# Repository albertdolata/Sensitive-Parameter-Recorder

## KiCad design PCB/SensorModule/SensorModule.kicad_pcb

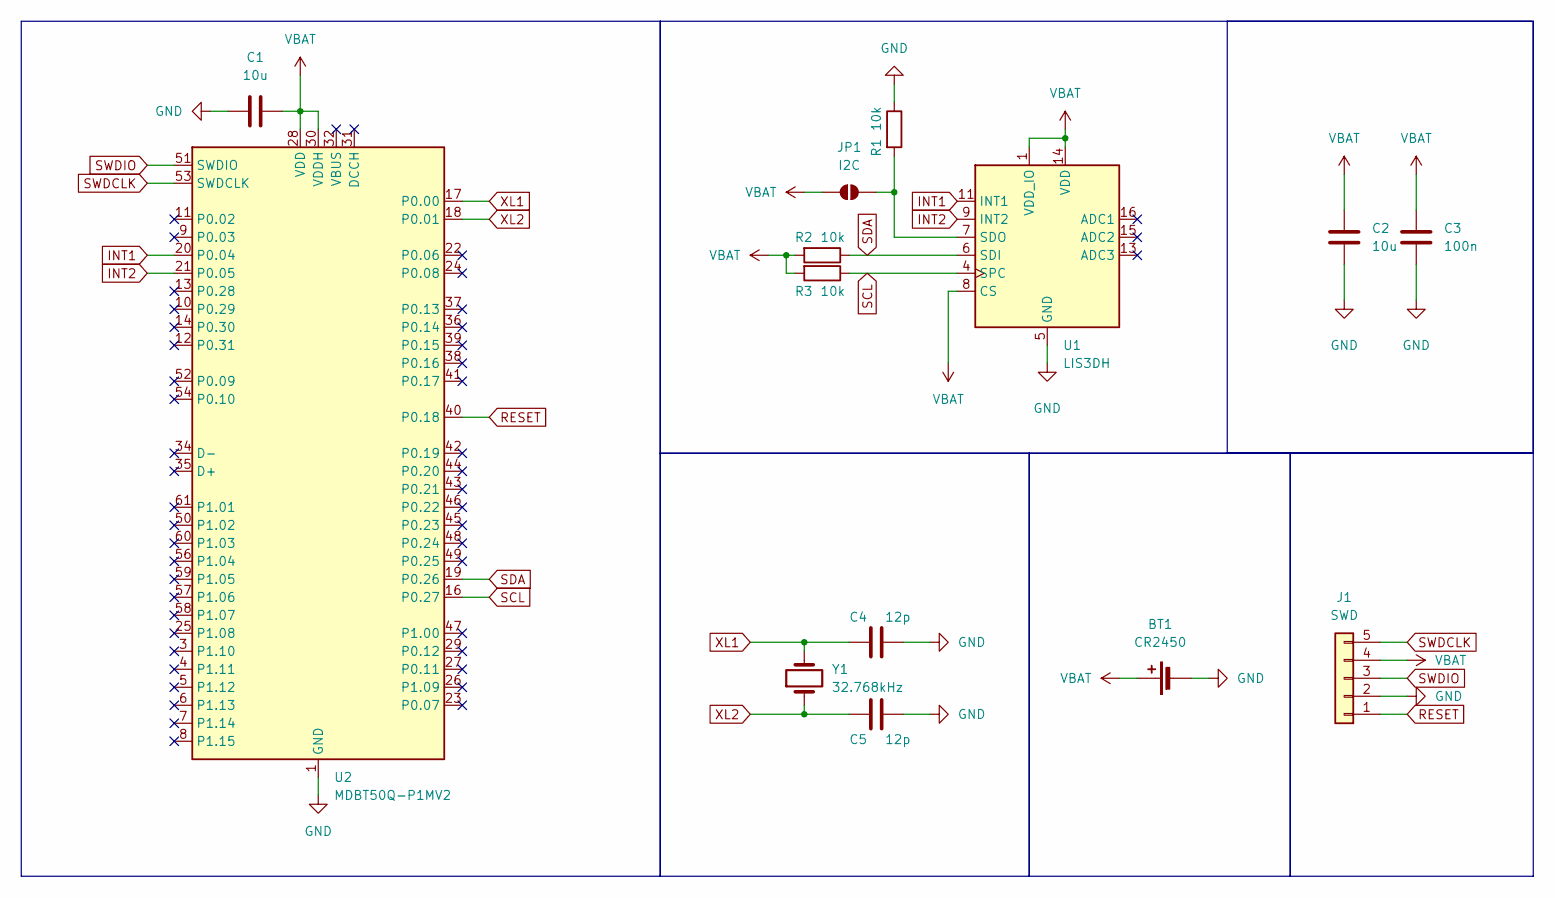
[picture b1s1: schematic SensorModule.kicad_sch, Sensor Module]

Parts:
BT1: CR2450; BatteryHolder_ComfortableElectronic_CH273-2450_1x2450
C1, C2: 10u; C_0402_1005Metric
C3: 100n; C_0402_1005Metric
C4, C5: 12p; C_0402_1005Metric
J1: SWD; PinHeader_1x05_P1.00mm_Vertical_SMD_Pin1Right
JP1: I2C; SolderJumper-2_P1.3mm_Open_TrianglePad1.0x1.5mm
R1, R2, R3: 10k; R_0402_1005Metric
U1: LIS3DH; LGA-16_3x3mm_P0.5mm_LayoutBorder3x5y
U2: MDBT50Q-P1MV2; Raytac_MDBT50Q
Y1: 32.768kHz; Crystal_SMD_3215-2Pin_3.2x1.5mm

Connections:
GND: BT1.2 (-), C1.1, C2.2, C3.2, C4.2, C5.2, J1.2, R1.1, U1.5 (GND), U1.10 (GND), U1.12 (GND), U2.1 (GND), U2.2 (GND), U2.15 (GND), U2.33 (GND), U2.55 (GND)
INT1: U1.11 (INT1), U2.20 (P0.04)
INT2: U1.9 (INT2), U2.21 (P0.05)
unnamed: JP1.1 (A), R1.2, U1.7 (SDO)
RESET: J1.1, U2.40 (P0.18)
SCL: R3.1, U1.4 (SPC), U2.16 (P0.27)
SDA: R2.1, U1.6 (SDI), U2.19 (P0.26)
SWDCLK: J1.5, U2.53 (SWDCLK)
SWDIO: J1.3, U2.51 (SWDIO)
VBAT: BT1.1 (+), C1.2, C2.1, C3.1, J1.4, JP1.2 (B), R2.2, R3.2, U1.1 (VDD_IO), U1.8 (CS), U1.14 (VDD), U2.28 (VDD), U2.30 (VDDH)
XL1: C4.1, U2.17 (P0.00), Y1.2
XL2: C5.1, U2.18 (P0.01), Y1.1

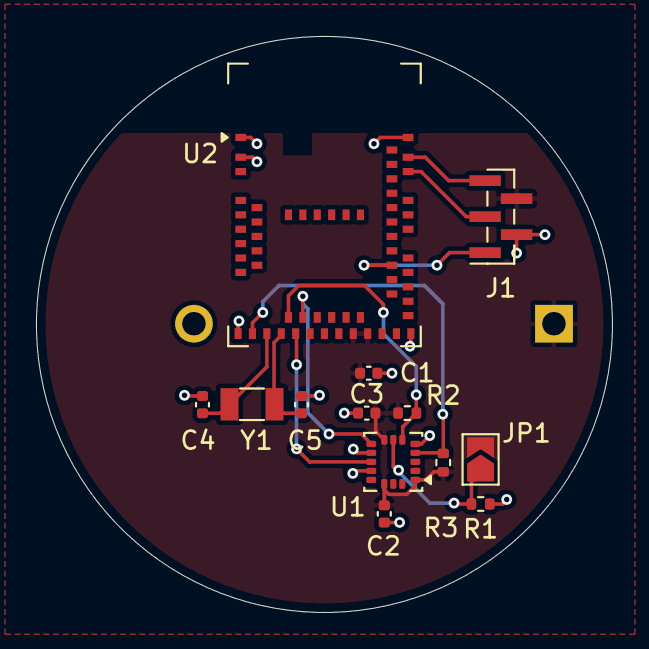
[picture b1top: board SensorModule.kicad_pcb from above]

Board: 2 copper layers, 32.0 x 32.0 mm, 14 parts (1 on the bottom side), 12 nets.

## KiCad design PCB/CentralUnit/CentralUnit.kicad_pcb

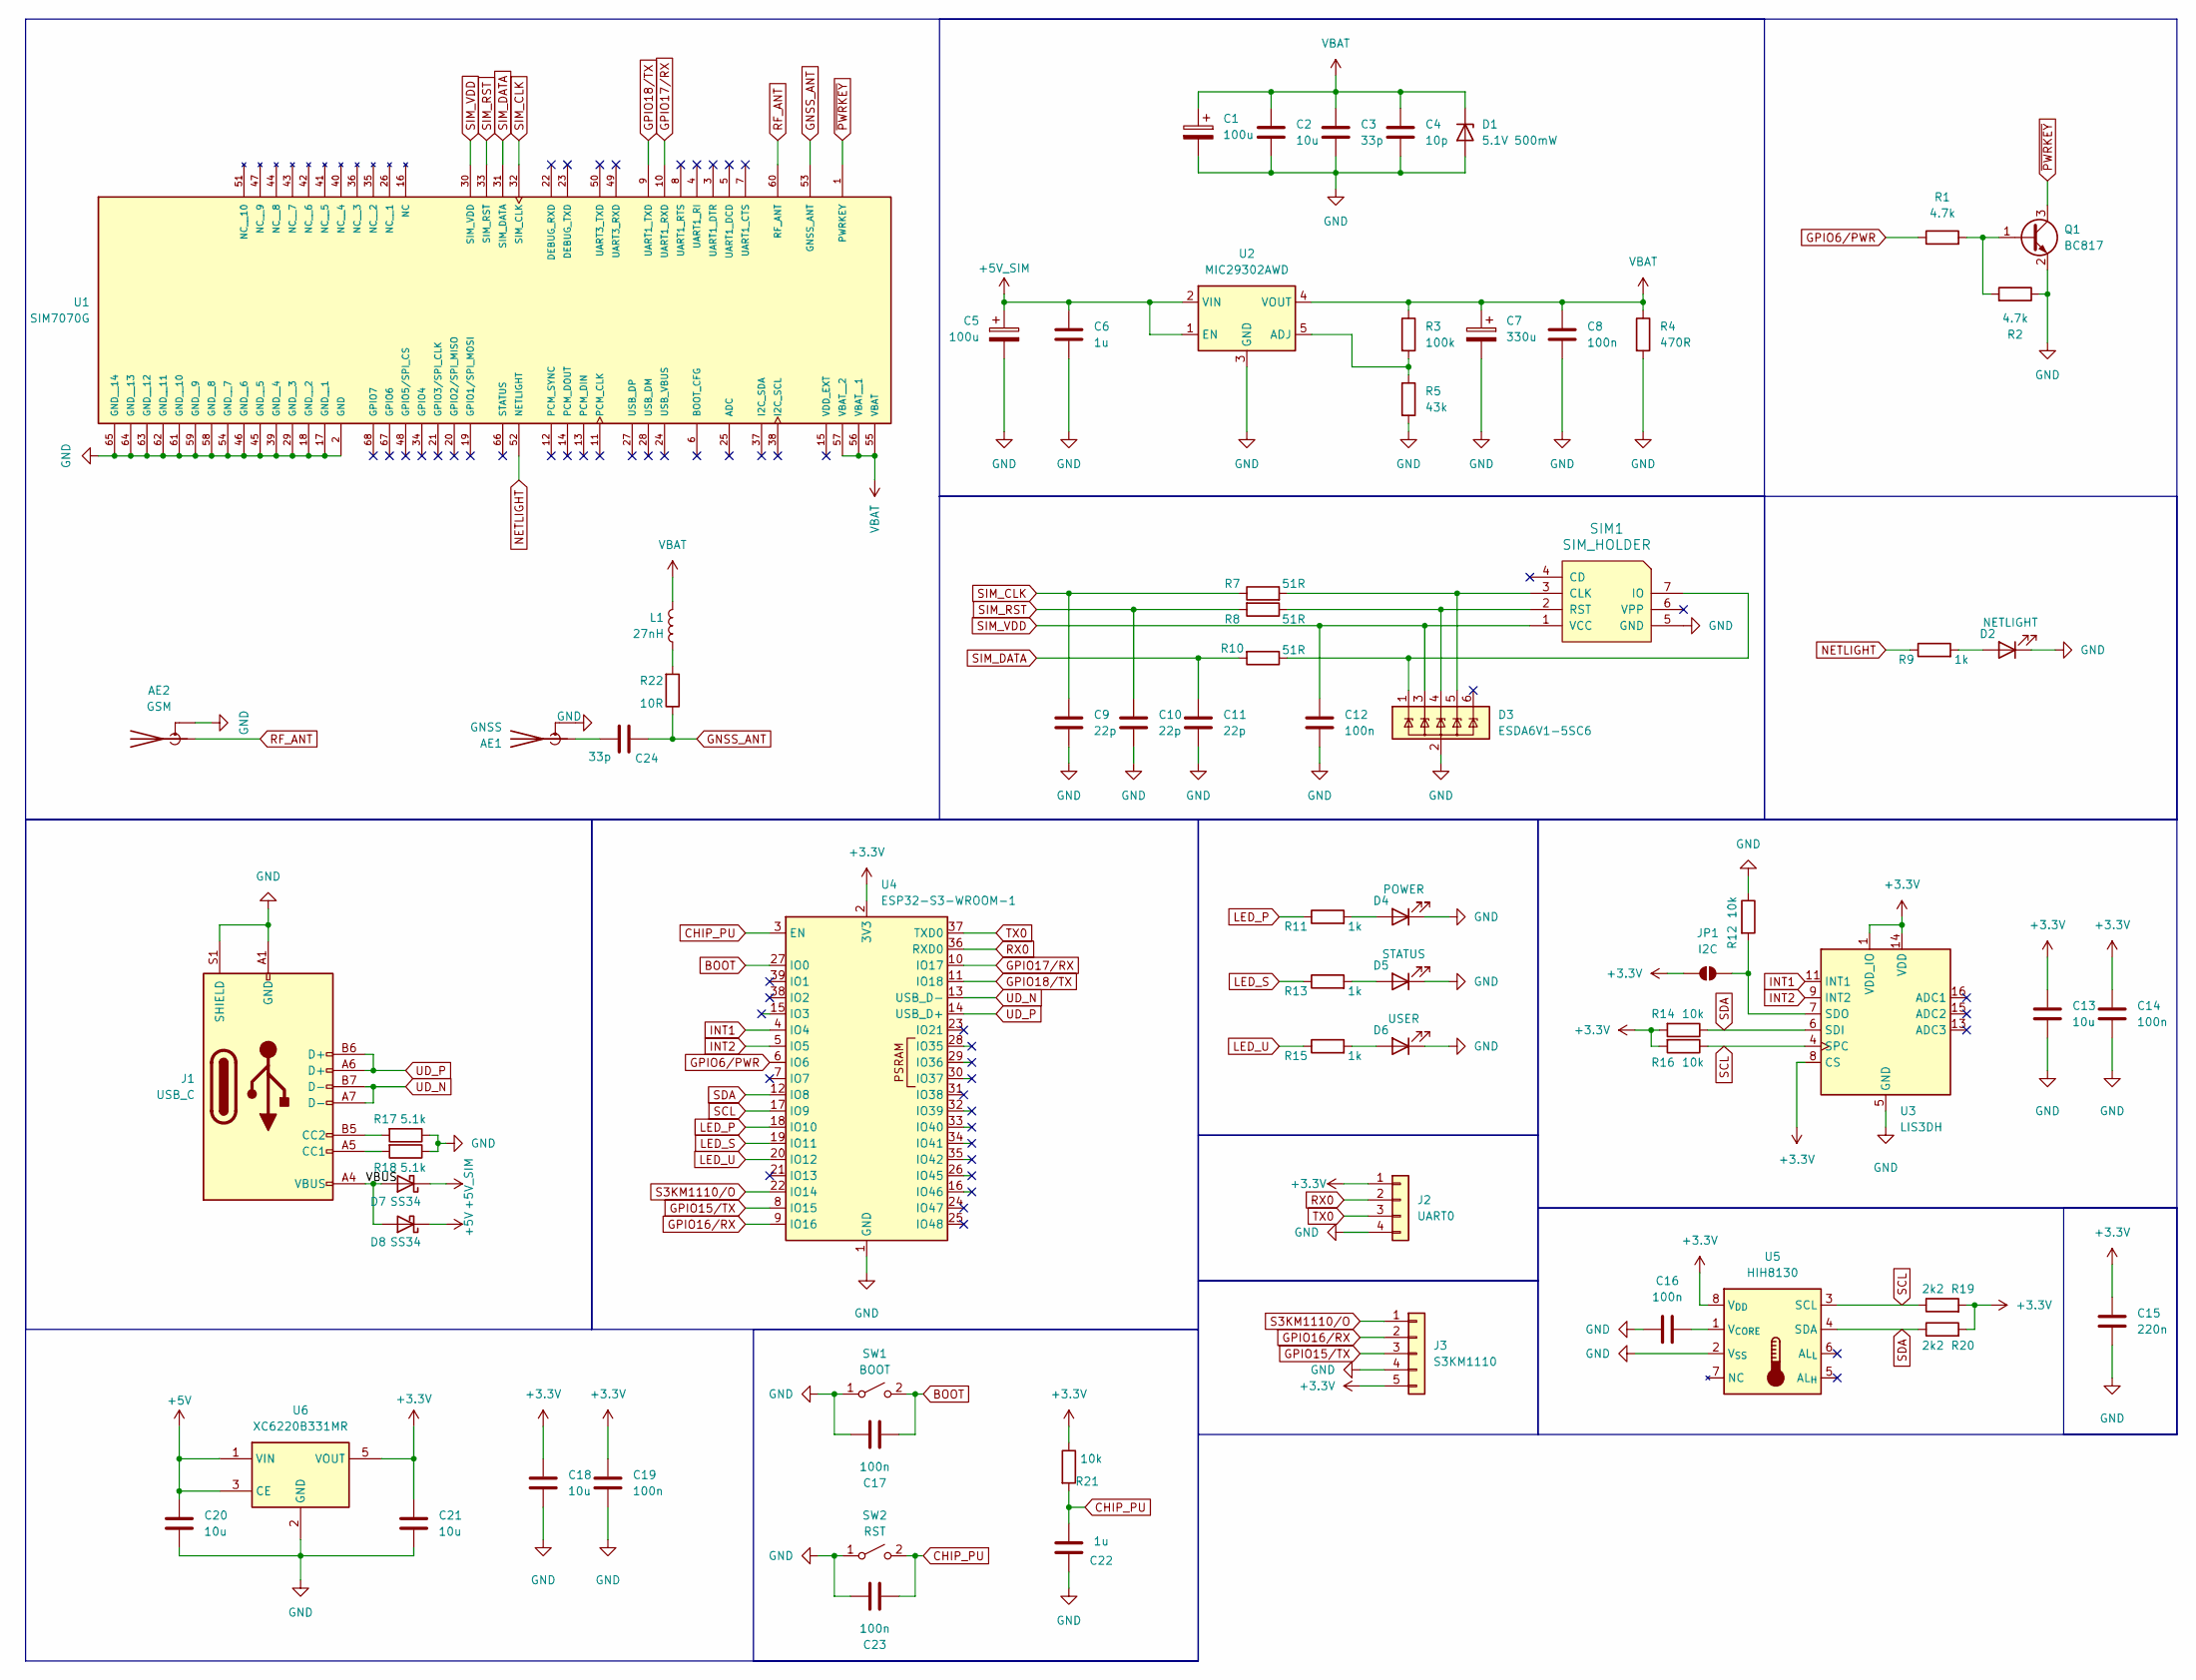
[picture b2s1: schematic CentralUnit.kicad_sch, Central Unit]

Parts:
AE1: GNSS; U.FL_Molex_MCRF_73412-0110_Vertical
AE2: GSM; U.FL_Molex_MCRF_73412-0110_Vertical
C1, C5: 100u; CP_EIA-3216-18_Kemet-A
C2, C13, C18, C20, C21: 10u; C_0402_1005Metric
C3, C24: 33p; C_0402_1005Metric
C4: 10p; C_0402_1005Metric
C6, C22: 1u; C_0402_1005Metric
C7: 330u; CP_EIA-6032-28_Kemet-C
C8, C12, C14, C16, C17, C19, C23: 100n; C_0402_1005Metric
C9, C10, C11: 22p; C_0402_1005Metric
C15: 220n; C_0402_1005Metric
D1: 5.1V 500mW; Nexperia_CFP3_SOD-123W
D2: NETLIGHT; LED_0805_2012Metric
D3: ESDA6V1-5SC6; SOT-23-6
D4: POWER; LED_0805_2012Metric
D5: STATUS; LED_0805_2012Metric
D6: USER; LED_0805_2012Metric
D7, D8: SS34; D_SMA
J1: USB_C; USB_C_Receptacle_HRO_TYPE-C-31-M-12
J2: UART0; PinHeader_1x04_P1.00mm_Vertical_SMD_Pin1Left
J3: S3KM1110; PinHeader_1x05_P2.54mm_Vertical
JP1: I2C; SolderJumper-2_P1.3mm_Open_TrianglePad1.0x1.5mm
L1: 27nH; L_0402_1005Metric
Q1: BC817; SOT-23
R1, R2: 4.7k; R_0402_1005Metric
R3: 100k; R_0402_1005Metric
R4: 470R; R_0402_1005Metric
R5: 43k; R_0402_1005Metric
R7, R8, R10: 51R; R_0402_1005Metric
R9, R11, R13, R15: 1k; R_0402_1005Metric; PART FIELD 1 ÌùÆ¬µç×è
R12, R14, R16, R21: 10k; R_0402_1005Metric
R17, R18: 5.1k; R_0402_1005Metric
R19, R20: 2k2; R_0402_1005Metric
R22: 10R; R_0402_1005Metric
SIM1: SIM_HOLDER; nanoSIM_SMN-303
SW1: BOOT; SW_Tactile_SPST_NO_Straight_CK_PTS636Sx25SMTRLFS
SW2: RST; SW_Tactile_SPST_NO_Straight_CK_PTS636Sx25SMTRLFS
U1: SIM7070G; SIM7070G_MODULE_SIM7070G; PARTREV V1.03
U2: MIC29302AWD; TO-252-5_1.27mm_TabPin3
U3: LIS3DH; LGA-16_3x3mm_P0.5mm_LayoutBorder3x5y
U4: ESP32-S3-WROOM-1
U5: HIH8130; SOIC-8_3.9x4.9mm_P1.27mm
U6: XC6220B331MR; SOT-23-5

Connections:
+3.3V: C13.1, C14.1, C15.1, C18.1, C19.1, C21.1, J2.1, J3.5, JP1.2 (B), R14.2, R16.2, R19.2, R20.2, R21.1, U3.1 (VDD_IO), U3.8 (CS), U3.14 (VDD), U4.2 (3V3), U5.8 (V_{DD}), U6.5 (VOUT)
+5V: C20.1, D8.1 (K), U6.1 (VIN), U6.3 (CE)
+5V_SIM: C5.1, C6.1, D7.1 (K), U2.1 (EN), U2.2 (VIN)
/VBUS: D7.2 (A), D8.2 (A), J1.A4 (VBUS), J1.A9 (VBUS), J1.B4 (VBUS), J1.B9 (VBUS)
BOOT: C17.2, SW1.2 (B), U4.27 (IO0)
CHIP_PU: C22.2, C23.2, R21.2, SW2.2 (B), U4.3 (EN)
GND: AE1.2 (Shield), AE2.2 (Shield), C1.2, C2.2, C3.2, C4.2, C5.2, C6.2, C7.2, C8.2, C9.2, C10.2, C11.2, C12.2, C13.2, C14.2, C15.2, C16.1, C17.1, C18.2, C19.2, C20.2, C21.2, C22.1, C23.1, D1.2 (A), D2.1 (K), D3.2 (GND), D4.1 (K), D5.1 (K), D6.1 (K), J1.A1 (GND), J1.A12 (GND), J1.B1 (GND), J1.B12 (GND), J1.S1 (SHIELD), J2.4, J3.4, Q1.2 (E), R2.1, R4.2, R5.2, R12.1, R17.1, R18.1, SIM1.5 (GND), SIM1.SH, SW1.1 (A), SW2.1 (A), U1.2 (GND), U1.17 (GND__1), U1.18 (GND__2), U1.29 (GND__3), U1.39 (GND__4), U1.45 (GND__5), U1.46 (GND__6), U1.54 (GND__7), U1.58 (GND__8), U1.59 (GND__9), U1.61 (GND__10), U1.62 (GND__11), U1.63 (GND__12), U1.64 (GND__13), U1.65 (GND__14), U2.3 (GND), U3.5 (GND), U3.10 (GND), U3.12 (GND), U4.1 (GND), U4.40 (GND), U4.41 (GND), U5.2 (V_{SS}), U6.2 (GND)
GNSS_ANT: C24.2, R22.1, U1.53 (GNSS_ANT)
GPIO6/PWR: R1.1, U4.6 (IO6)
GPIO15/TX: J3.3, U4.8 (IO15)
GPIO16/RX: J3.2, U4.9 (IO16)
GPIO17/RX: U1.10 (UART1_RXD), U4.10 (IO17)
GPIO18/TX: U1.9 (UART1_TXD), U4.11 (IO18)
INT1: U3.11 (INT1), U4.4 (IO4)
INT2: U3.9 (INT2), U4.5 (IO5)
LED_P: R11.1, U4.18 (IO10)
LED_S: R13.1, U4.19 (IO11)
LED_U: R15.1, U4.20 (IO12)
NETLIGHT: R9.1, U1.52 (NETLIGHT)
unnamed: AE1.1 (A), C24.1
unnamed: D2.2 (A), R9.2
unnamed: D3.1 (IO1), R10.1, SIM1.7 (IO)
unnamed: D3.4 (IO3), R8.1, SIM1.2 (RST)
unnamed: D3.5 (IO4), R7.2, SIM1.3 (CLK)
unnamed: D4.2 (A), R11.2
unnamed: D5.2 (A), R13.2
unnamed: D6.2 (A), R15.2
unnamed: J1.A5 (CC1), R18.2
unnamed: J1.B5 (CC2), R17.2
unnamed: JP1.1 (A), R12.2, U3.7 (SDO)
unnamed: L1.2, R22.2
unnamed: Q1.1 (B), R1.2, R2.2
unnamed: R3.2, R5.1, U2.5 (ADJ)
unnamed: C16.2, U5.1 (V_{CORE})
RF_ANT: AE2.1 (A), U1.60 (RF_ANT)
RX0: J2.2, U4.36 (RXD0)
S3KM1110/O: J3.1, U4.22 (IO14)
SCL: R16.1, R19.1, U3.4 (SPC), U4.17 (IO9), U5.3 (SCL)
SDA: R14.1, R20.1, U3.6 (SDI), U4.12 (IO8), U5.4 (SDA)
SIM_CLK: C9.1, R7.1, U1.32 (SIM_CLK)
SIM_DATA: C11.1, R10.2, U1.31 (SIM_DATA)
SIM_RST: C10.1, R8.2, U1.33 (SIM_RST)
SIM_VDD: C12.1, D3.3 (IO2), SIM1.1 (VCC), U1.30 (SIM_VDD)
TX0: J2.3, U4.37 (TXD0)
UD_N: J1.A7 (D-), J1.B7 (D-), U4.13 (USB_D-)
UD_P: J1.A6 (D+), J1.B6 (D+), U4.14 (USB_D+)
VBAT: C1.1, C2.1, C3.1, C4.1, C7.1, C8.1, D1.1 (K), L1.1, R3.1, R4.1, U1.55 (VBAT), U1.56 (VBAT__1), U1.57 (VBAT__2), U2.4 (VOUT)
~PWRKEY: Q1.3 (C), U1.1 (PWRKEY)

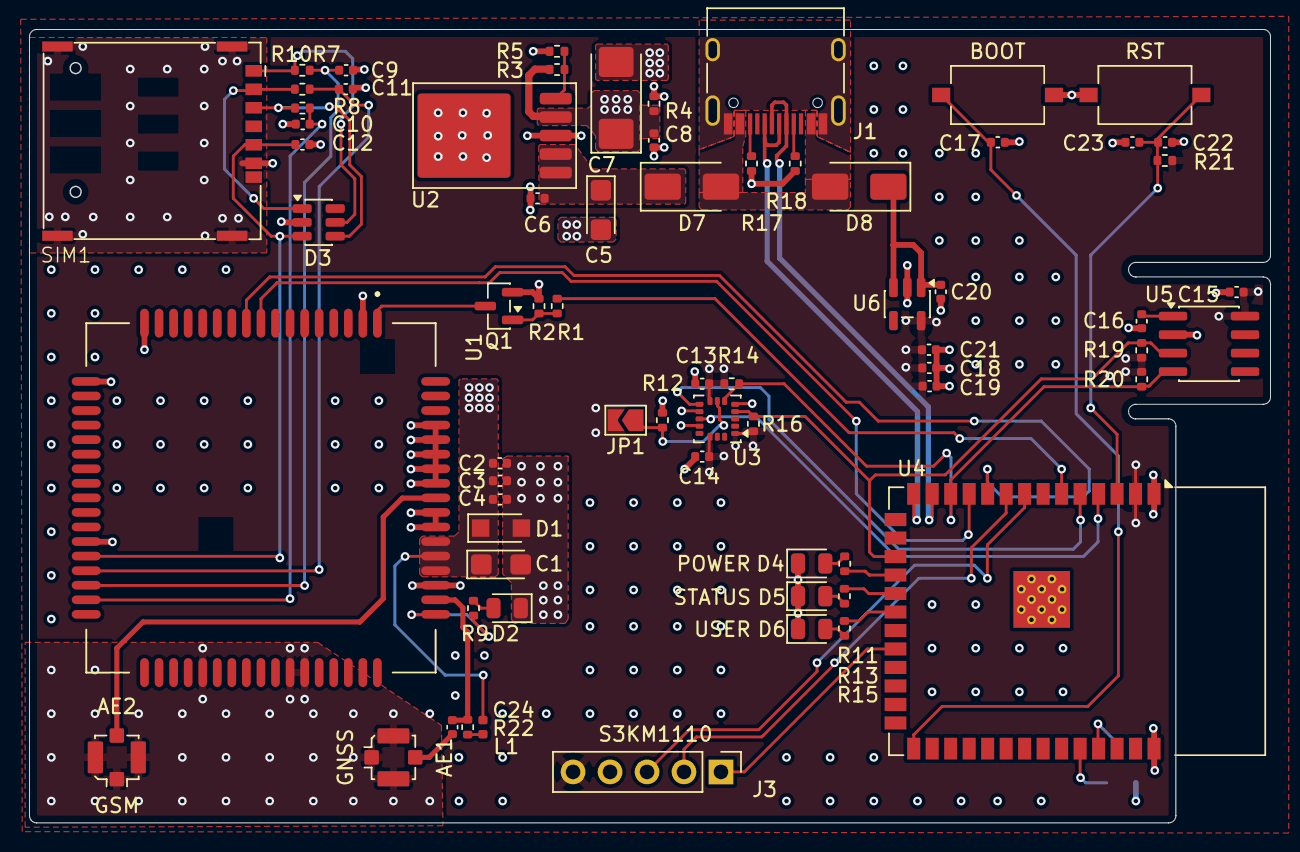
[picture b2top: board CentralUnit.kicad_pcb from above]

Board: 4 copper layers, 85.2 x 54.5 mm, 70 parts (1 on the bottom side), 48 nets.

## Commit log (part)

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2026-04-02 Create project
2026-04-02 Create abstract class Sesnor
2026-04-02 Create class TempHumSenesor
2026-04-02 Create clas AccelSensor
2026-04-02 Create testing programm in main file
2026-04-02 Fix format
2026-04-02 Refactor: add macro for number of sensors, add starting logs, fix delay logic
2026-04-02 Create class ContactSensor
2026-04-02 Create class PresenceSensor
2026-04-02 Change logic of function readData in ContactSensor
2026-04-02 Write code of class PresenceSensor
2026-04-02 Upadte main fucntion, add contact and presence sensor object to the array of sensors
2026-04-02 Create file for CloudManager class
2026-04-02 Add ThingSpeak library to the project
2026-04-02 Write code of class CloudManager
2026-04-02 Refactor class Sensor, add temporery fields for sensor values
2026-04-02 Refactor function readData in class TempHumSensor, store BME230 readings in shared Sensor values1-3
2026-04-02 Refactor classes AccelSensor, ContactSensor, PresennceSensor, now sotres it's reading in shared value Sensor value1
2026-04-02 Fix: moved fields form private to public
2026-04-02 Update main file, add ThingSpeak feature
2026-04-12 Create Bluetooth Sensor Manager file
2026-04-12 Create class BLESensor
2026-04-12 Refactor: Class BLESensorManager now assings recived data to given sensor
2026-04-12 Future: add support of bluetooth
2026-04-12 Future: Add start of BLE radar
2026-04-13 Refactor: Update code to suppport new BLESensors
2026-04-13 Update: class now is supporting 3 sensors
2026-04-13 Refactor: function init constantly return true
2026-04-13 Change in platformio.ini
2026-04-13 Debug: add code for easier debugging while testing with real devices
2026-04-14 Update: extended fields in class Sensor for new data
2026-04-14 Update: changed names of variables for recived data from ble and expected data that should be recived
2026-04-14 Update: deleted field shake - not usuable for prototape, updatethe assigning of values in switch section
2026-04-14 Update: the data that is set in the ThingSpeak fields has been changed
2026-04-26 Create class for GPS service
2026-04-26 Add GPS support to main file
2026-04-26 Variable edit: changed sensor fileds sent to ThingSpeak for debugging
2026-05-04 Add PCB KiCAD 9..0 Files
2026-05-10 pliki z konfiguracją esp32 i simcoma
    Pliki z konfiguracją esp32 i sim7000, funkcję pozwalające uruchomić sim'a, zalogować się do sieci, pobrać parametry stacji bazowej i wysłać przez mqtt. Do dodania, obsługa rzeczywistych sensorów i zb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
2026-05-22 Add new item to ignore
2026-05-22 Moved files to appropriate project code folders
2026-05-22 Add necceseary library to data_send_service.cpp - freertos/queue.h
2026-05-22 expanded the fields of sensor_data_t structure for all sensors
2026-05-22 function send_at_cmd now is global function
2026-05-22 Add declaration of function send_at_cmd in sim7000_core file
2026-05-22 Refactor of class GPSManager - class now is using sent_at_cmd function
2026-05-22 Fix typo
2026-05-22 Integration main code with main code of esp_simcom
2026-05-22 Expand json format in data_send_service
2026-05-22 Commented flags out because by default without specifying bed parameters with zeros - an error
2026-05-29 Change Uart baud rate to fit my simcom in sim7000_core.cpp | fix assignment of current_data schock variable
2026-05-29 Add new field for time stamps of data in sensor_data_t
2026-05-29 Add function to parse time form gps data whichc is called in parseResponse function | Add getter for timestamps parsed by new function
2026-05-29 Add ESP32 internal RTC synchronization with GPS
    - Add setESP32Time() to update internal timer when GPS has fix
    - Update current_data.timestamp to source time from ESP32 RTC
2026-05-29 Create test function for creating file in flash memory, write text into the file and then read text from it
2026-05-29 Create function to save data in flash memory
2026-05-29 Create function to sent backup data by data_service_push()
2026-05-29 Refactor: extract data assignment of sensor_data_t to assignDataToStruct function
2026-05-29 Add data backup logic in main
2026-05-29 Create init function for SPIFFS and add call of it in setup()
2026-05-29 Refactor: extract sim7000 if statements to SIMComInit function
2026-05-29 Refactor: extract sensor table initialization logic to SensorTableInit function
2026-05-29 Refactor: extract BLE logic to BLEInit function
2026-05-29 Refactor: extract readData from sensor logic to readDataFromSensor function
2026-05-29 Refactor: extract data logic to sendDataToServer function
2026-05-29 Fix bugs after testing offline data storing
    - Timestamp is now correctly saved in offline data
    - Fixed looping problem with data recovery from internal flash memory
2026-06-03 Temp-hum sensor driver implementation
2026-06-08 Obsługa sensora mmw
2026-06-12 New JSON data format
2026-06-12 Refactor: changed values for secondary central data
2026-06-12 Refacotr: update class for TH06 sensor
2026-06-12 Refacotr: update class for LIS3DH accelerometer
2026-06-12 Refacotr: update class for S3KM1110 mmWave Radar - easire approach
2026-06-12 Add libraries to the project
2026-06-13 Create new class for BLE pallet sensor
2026-06-13 Create new class for BLE secondary central
2026-06-13 Refactor: BLEPalletSensor now is compatible with nrf sent data
2026-06-13 Refactor: BLESensorManager now is compatible with data sent by nrf
2026-06-15 Fix name of the class
2026-06-15 Create MainCentralSensorManager class
2026-06-15 Refactor: rename struct to fix name collision
2026-06-15 Upadte: add proper fields in struct for sensor data
2026-06-15 Fix comment
2026-06-16 Fix format of file with class MainCentralSensorManager
2026-06-16 Refactor: Integrate MainCentralSensorManager and clean up main.cpp
2026-06-16 Fix: resolve switch case compile error in BLESensorManager
2026-06-16 Fix: update JSON generator with correct fields and data types
2026-06-16 Update: add proper fields to struct for accelerometer data
2026-06-16 Update add accel data in JSON generator
2026-06-16 Update: function fillSensorData now assigns proper data in data struct
2026-06-16 Update project dependencies
2026-06-16 Add usage of LEDs on board
2026-06-16 Update rx/tx pin for hardware
2026-06-16 Update sim init function for testing hardware
2026-06-18 Update: replace the code file for sim7070 configuration
2026-06-18 Rename header file for simcom7070
2026-06-18 Update: Integrate GPSManager with SIM7070E
    - Add pause/resume functions to control GPS power
    - Fix include path
2026-06-18 Fix typos to match proper sim7070 functions
2026-06-18 Fix: Increase stack size for data_sender_task to 8KB
    - Resolves Guru Meditation Error (Stack Overflow) when processing massive offline data backlog from SPIFFS
2026-06-18 Refactor: Update main.cpp for SIM7070E and prepare for hardware tests
    - Rename all sim7000_* function calls to sim7070_* to match the new core
    - Enable global INFO logs and set SIM7070_GPRS to DEBUG level
    - Temporarily comment out GPS routines pending hardware rework
2026-06-23 Refactor: switch to MAC address filtering and remoce second pallet sensor
2026-06-23 Fix: implement MQTT disconnect to prevent RF transceiver crash Resolved hardware-level conflicts in the SIM7070E modem caused by simultaneous RF demands from active PDP/MQTT contexts and GNSS wake-up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
    sim7070_core.h & sim_mod.c:
    - Added sim7070_mqtt_disconnect() to safely terminate MQTT sessions (AT+SMDISC) and deactivate the PDP context (AT+CNACT=0,0).
    - Refactored the IP allocation active polling loop (Active Polling) to improve connection stability and prevent T-Mobile network rejections.
    data_send_service.h & data_send_service.cpp:
    - Updated the data_sender_task to monitor queue size via uxQueueMessagesWaiting().
    - The background task now explicitly closes all network connections when
2026-06-23 Refactor: add MAC addresses and implement initial GPS fix waiting
2026-06-25 Fix: cell data is now correctly recived from simcom
2026-06-25 refactor: restructure offline storage and prevent FSM deadlocks
    - Relocate SPIFFS backup logic to data_send_service to decouple it from main state machine.
    - Reduce data_queue size to 1 and trigger automatic SPIFFS save on RAM full.
    - Remove blocking vTaskDelay in data_sender_task to prevent GSM/GNSS RF collisions.
    - Increase JSON buffer to 768 bytes and add motion_detected_p1 (p1mot) to payload.
    - Optimize sendBackupData to bypass RAM queue, reducing Flash memory wear.
2026-06-25 Fix: decouple power state from fix status and resolve state machine bugs
    - Introduce 'fixStatus' to track satellite fix independently from module power state ('isON').
    - Add 'isPowered()' getter to safely expose hardware state to the main state machine.
    - Fix inverted guard clause in 'resume()' and ensure 'fixStatus' and timestamps are cleared on wake.
    - Add guard clause in 'update()' to prevent polling the GNSS baseband when powered off.
    - Remove raw NMEA serial debug prints to reduce log clutter.
2026-06-25 Update: add assignment of 'motion_detected_p1' from palletSensor1 in MainCentralSensorManager
2026-06-26 Refactor: implement non-blocking FSM and decouple core services
    - Replace linear, delay-based main loop with a non-blocking Finite State Machine (FSM).
    - Delegate all SPIFFS offline backup logic entirely to 'data_send_service'.
    - Offload BLE scanning to a dedicated FreeRTOS background task ('bleScanTask') pinned to Core 0.
    - Add 120-second timeout for GNSS fix acquisition in State 0 to prevent FSM stalling.
    - Implement Anti-Spoofing logic (FSM State 1) to fetch BTS cell info with a 15-second timeout.
    - Safely multiplex GNSS and GSM radio usage by pausing/resuming GPS based on FSM states.
2026-06-26 Refactor: remove serial prints and restrict global debug levels to errors
2026-06-27 Refactor: implement modular OOP architecture, separate headers from sources, and isolate main.cpp logic
2026-06-28 Update/Fix: LED STATUS blinks when got package form ble devices, LED USER lights up while system in sending data state, fixed backup data storage system,
2026-06-28 Fix: resolve bootloop, fix CREG/CGREG network check, and implement self-recovery mechanism
2026-06-29 Update/Fix: implement fault-tolerance and SPIFFS protection
    Modem & Network Recovery:
    - Add hardware-level modem recovery after 3 consecutive connection failures.
    - Fix IP zombie state: shift failure counter reset to End-to-End ACK (MQTT success) rather than just CREG/CGREG attach.
    - Implement global watchdog in main loop to trigger ESP.restart() if the sending cycle exceeds 3 minutes.
    SPIFFS Protection & Data Integrity:
    - Secure file operations with FreeRTOS Mutex to prevent read/write/delete race conditions.
2026-06-29 Build: unlock full 8MB flash and expand SPIFFS partition
    Added custom partitions.csv to utilize the full 8MB hardware flash of the ESP32-S3. Reallocated space to provide ~5MB for the SPIFFS data partition, significantly increasing offline backlog capacity.
2026-06-29 Docs: add Doxyfile for doxygen configuration, add docs folder to gitignore
